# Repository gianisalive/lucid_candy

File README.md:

# Lucid Candy

A bare minimum 8 channel EEG board with TI ads1299 chip. It can be driven with any microcontroller that has 3.3V logic. Multiple boards can be chained together to record with 16 or 24 channels. This repository includes KiCad files and SPI example.

## Disclaimer
It still needs a lot of improvement, professional guidance and review. In no way it's fully tested to perform under clinical setting. Please use basic principles to test and evaluate before using it. All suggestions are highly appreciated: gianisalive@gmail.com

## Who should use it?
No one really should, but if you're a newbie in electronics, software, and neuroscience, and want to learn more by building, then this might be a thing for you. If you're just looking for an affordable EEG, there're better open source ones out there, such as [OpenBCI](https://openbci.com/).

## Files & Locations
|-- lucid_candy  
|---- component_datasheet------important datasheet of the components used for the board  
|---- e_component---------------all the KiCad pcb footprint (from SnapEDA) for the components  
|---- eeg------------------------KiCad design files  
|---- firmware-------------------example of Arduino DUE communicating with the board via SPI  
|---- gerber_zip-----------------same file used to produce the current board with JLCPCB  

## Schematics
The philosophy with current version of the design is to work within TI's recommendation, and choose components with least amount of tolerance/inductance to develope a baseline. In the future, any design improvement can be evaluated/compared to the current design.

## Components
All the component used can be found [here](https://docs.google.com/spreadsheets/d/1N4UGuHjUGolRgQoIL3MemhwEijfZmJlSR52b1LrSyF4/edit?usp=sharing). Some of these are pretty over priced. In most situations, you can probably get away with cheaper parts.

## Programming in a nutshell
**Overview:**  
- Data are transfered via SPI MODE1 with MSB first
- Data are retrieve with no-op command 0x00
- Chip has an internal clock. If BYOO (bring your own oscillator), then connect it to CLK pin, and tie CLKSEL low.  

**Power up sequence:**  
- Set CLKSEL pin high to enable internal oscillator
- Set RESET pin high, and make sure VCAP1 is settled around 1.1V
- Send reset command, and at this point DRDY pin should toggle at around 250Hz
- Send SDATAC (stop data continuous) command
- Set CONFIG1(0x01), CONFIG2(0x02) and CONFIG3(0x03)
- Set CHnSET (single ended, double ended or generate test signal)

**Data conversion:**  
- After sending RDATA or RDATAC command, data is returned on the second rising edge of the DRDY pin
- Initial 3 bytes are status data, and it always starts with 1100. Then it'll transfer 3 bytes of data per channel. An 8 channel board will have 8 * 3 + 3 = 27 bytes of data
- Data are structured in 2's compliment. The MSB is used to determin whether the value is positive or negative
- V = LSB * (2 * 4.5 / 24) / (2 ^ 24) // LSB = decimal value of 3 bytes channel data

## Testing
Fully assembled device with current Arduino firmware is tested with a calibrated Keysight DSOX1204G oscilloscope/function generator.

## Chanllenges
In a nutshell, eliminating noises and extracting the signal is one of the most chanllenging part when it comes to designing the hardware and the software.  
Neurons communcate via electrical signals (Action Potentials). When neurons are ready to send signals to neighboring neurons, they produce about 100 mV spike in less than 3 ms. These signals are further attenuated (reduction in signal strength) by the surrounding anatomical structures. When the electrode receives the signal, it's been attenuated to uV scale. In order to extract the signals, we need to filter out the noise with minimal distortion to the signal. There're few methods suggest that're yet to be implemented, such as bandpass filter, CleanLine and infinite impulse response.

## Miscellaneous
Some silly questions I asked:
 - [voltage offset](https://e2e.ti.com/support/data-converters/f/73/p/912858/3374371#3374371)

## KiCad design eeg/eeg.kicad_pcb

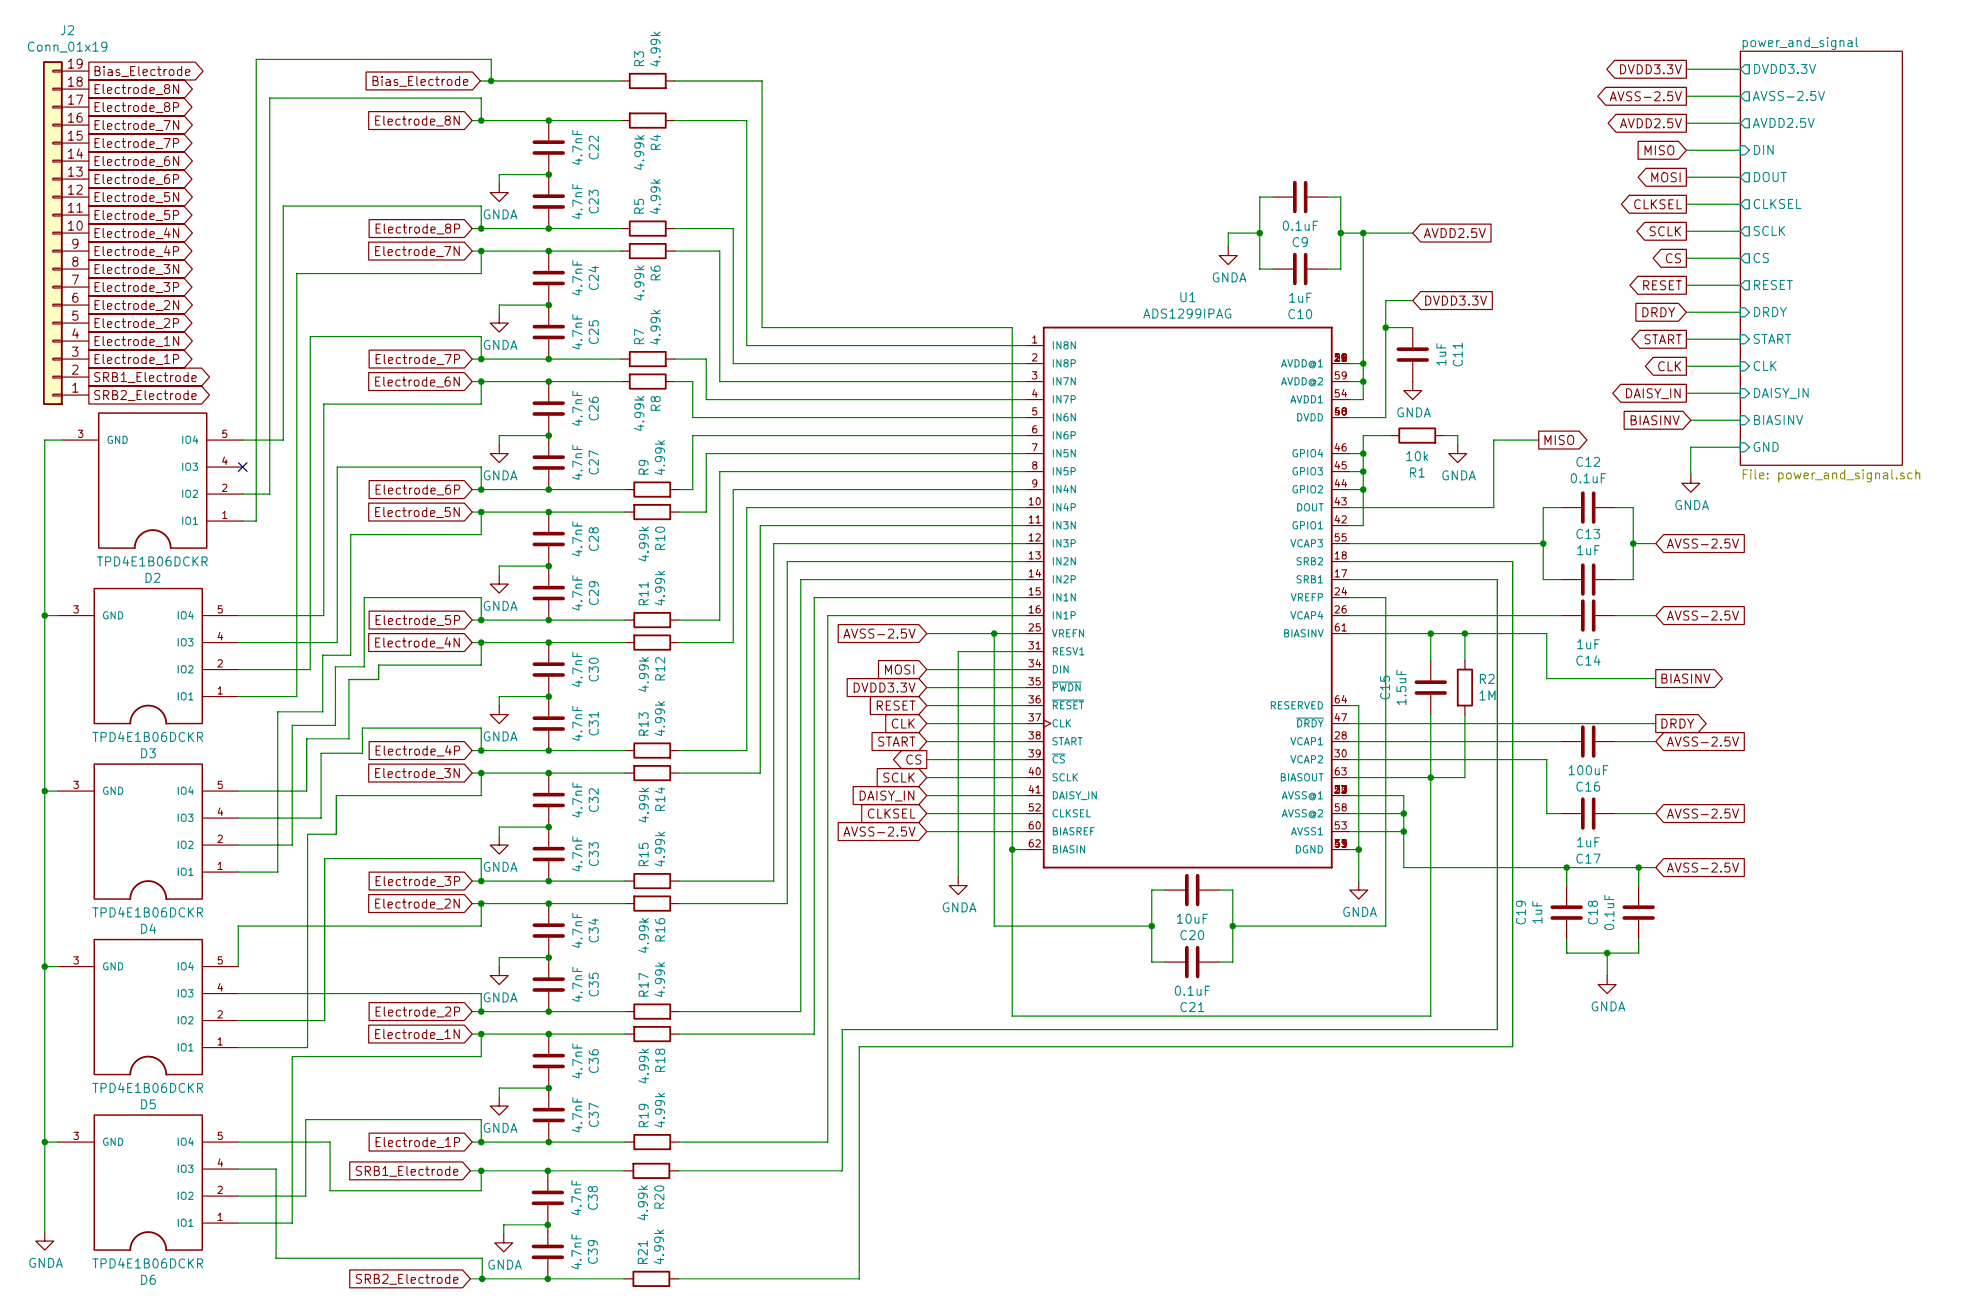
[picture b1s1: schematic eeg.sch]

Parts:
C9, C12, C18, C21: 0.1uF; C_0805_2012Metric_Pad1.15x1.40mm_HandSolder
C10, C11, C13, C14, C17, C19: 1uF; C_0805_2012Metric_Pad1.15x1.40mm_HandSolder
C15: 1.5uF; C_0805_2012Metric_Pad1.15x1.40mm_HandSolder
C16: 100uF; C_1210_3225Metric_Pad1.42x2.65mm_HandSolder
C20: 10uF; C_0805_2012Metric_Pad1.15x1.40mm_HandSolder
C22, C23, C24, C25, C26, C27, C28, C29, C30, C31, C32, C33, C34, C35, C36, C37, C38, C39: 4.7nF; C_0805_2012Metric_Pad1.15x1.40mm_HandSolder
D2, D3, D4, D5, D6: TPD4E1B06DCKR
J2: Conn_01x19; PinHeader_1x19_P2.54mm_Vertical
R1: 10k; R_0805_2012Metric_Pad1.15x1.40mm_HandSolder
R2: 1M; R_1206_3216Metric_Pad1.42x1.75mm_HandSolder
R3, R4, R5, R6, R7, R8, R9, R10, R11, R12, R13, R14, R15, R16, R17, R18, R19, R20, R21: 4.99k; R_0805_2012Metric_Pad1.15x1.40mm_HandSolder
U1: ADS1299IPAG

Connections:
AVDD2.5V: C9.1, C10.1, U1.19 (AVDD@1), U1.21 (AVDD@1), U1.22 (AVDD@1), U1.54 (AVDD1), U1.56 (AVDD@1), U1.59 (AVDD@2); also elsewhere on the board
AVSS-2.5V: C12.2, C13.2, C14.1, C16.1, C17.1, C18.2, C19.2, C20.2, C21.2, U1.20 (AVSS@1), U1.23 (AVSS@1), U1.25 (VREFN), U1.32 (AVSS@1), U1.53 (AVSS1), U1.57 (AVSS@1), U1.58 (AVSS@2), U1.60 (BIASREF); also elsewhere on the board
BIASINV: C15.2, R2.1, U1.61 (BIASINV); also elsewhere on the board
Bias_Electrode: D2.1 (IO1), J2.19, R3.1
CLK: U1.37 (CLK); also elsewhere on the board
CLKSEL: U1.52 (CLKSEL); also elsewhere on the board
CS: U1.39 (~CS~); also elsewhere on the board
DAISY_IN: U1.41 (DAISY_IN); also elsewhere on the board
DRDY: U1.47 (~DRDY~); also elsewhere on the board
DVDD3.3V: C11.1, U1.35 (~PWDN~), U1.48 (DVDD), U1.50 (DVDD); also elsewhere on the board
Electrode_1N: C36.1, D6.1 (IO1), J2.4, R18.2
Electrode_1P: C37.2, D6.2 (IO2), J2.3, R19.1
Electrode_2N: C34.1, D5.5 (IO4), J2.6, R16.2
Electrode_2P: C35.2, D5.4 (IO3), J2.5, R17.1
Electrode_3N: C32.1, D5.1 (IO1), J2.8, R14.2
Electrode_3P: C33.2, D5.2 (IO2), J2.7, R15.1
Electrode_4N: C30.1, D4.5 (IO4), J2.10, R12.2
Electrode_4P: C31.2, D4.4 (IO3), J2.9, R13.1
Electrode_5N: C28.1, D4.1 (IO1), J2.12, R10.2
Electrode_5P: C29.2, D4.2 (IO2), J2.11, R11.1
Electrode_6N: C26.1, D3.5 (IO4), J2.14, R8.2
Electrode_6P: C27.2, D3.4 (IO3), J2.13, R9.1
Electrode_7N: C24.1, D3.1 (IO1), J2.16, R6.2
Electrode_7P: C25.2, D3.2 (IO2), J2.15, R7.1
Electrode_8N: C22.1, D2.2 (IO2), J2.18, R4.2
Electrode_8P: C23.2, D2.5 (IO4), J2.17, R5.1
GNDA: C9.2, C10.2, C11.2, C18.1, C19.1, C22.2, C23.1, C24.2, C25.1, C26.2, C27.1, C28.2, C29.1, C30.2, C31.1, C32.2, C33.1, C34.2, C35.1, C36.2, C37.1, C38.2, C39.1, D2.3 (GND), D3.3 (GND), D4.3 (GND), D5.3 (GND), D6.3 (GND), R1.2, U1.31 (RESV1), U1.33 (DGND), U1.49 (DGND), U1.51 (DGND), U1.64 (RESERVED); also elsewhere on the board
MISO: U1.43 (DOUT); also elsewhere on the board
MOSI: U1.34 (DIN); also elsewhere on the board
unnamed: C12.1, C13.1, U1.55 (VCAP3)
unnamed: C14.2, U1.26 (VCAP4)
unnamed: C15.1, R2.2, R3.2, U1.62 (BIASIN), U1.63 (BIASOUT)
unnamed: C16.2, U1.28 (VCAP1)
unnamed: C17.2, U1.30 (VCAP2)
unnamed: C20.1, C21.1, U1.24 (VREFP)
unnamed: R1.1, U1.42 (GPIO1), U1.44 (GPIO2), U1.45 (GPIO3), U1.46 (GPIO4)
unnamed: R4.1, U1.1 (IN8N)
unnamed: R5.2, U1.2 (IN8P)
unnamed: R6.1, U1.3 (IN7N)
unnamed: R7.2, U1.4 (IN7P)
unnamed: R8.1, U1.5 (IN6N)
unnamed: R9.2, U1.6 (IN6P)
unnamed: R10.1, U1.7 (IN5N)
unnamed: R11.2, U1.8 (IN5P)
unnamed: R12.1, U1.9 (IN4N)
unnamed: R13.2, U1.10 (IN4P)
unnamed: R14.1, U1.11 (IN3N)
unnamed: R15.2, U1.12 (IN3P)
unnamed: R16.1, U1.13 (IN2N)
unnamed: R17.2, U1.14 (IN2P)
unnamed: R18.1, U1.15 (IN1N)
unnamed: R19.2, U1.16 (IN1P)
unnamed: R20.1, U1.17 (SRB1)
unnamed: R21.2, U1.18 (SRB2)
RESET: U1.36 (~RESET~); also elsewhere on the board
SCLK: U1.40 (SCLK); also elsewhere on the board
SRB1_Electrode: C38.1, D6.5 (IO4), J2.2, R20.2
SRB2_Electrode: C39.2, D6.4 (IO3), J2.1, R21.1
START: U1.38 (START); also elsewhere on the board

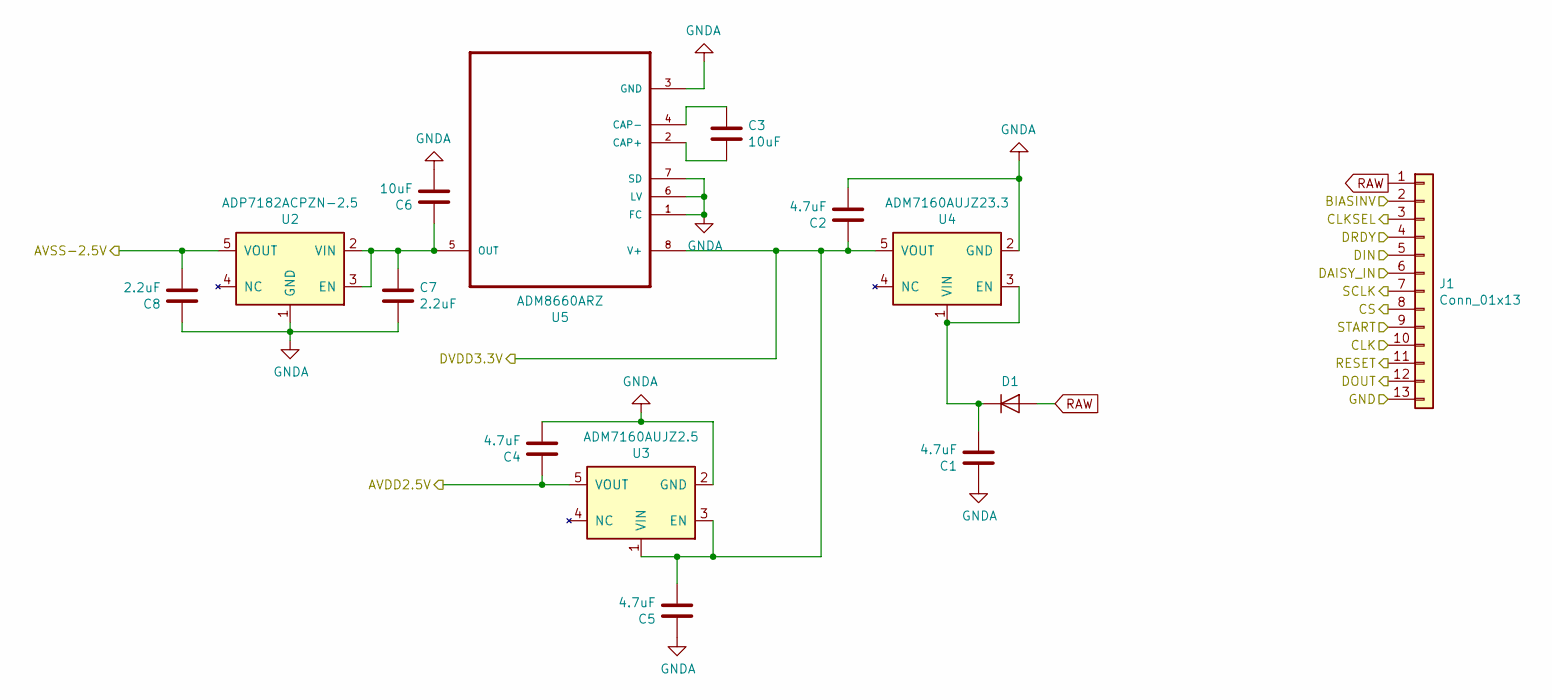
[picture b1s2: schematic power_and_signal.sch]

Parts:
C1, C2, C4, C5: 4.7uF; C_0805_2012Metric_Pad1.15x1.40mm_HandSolder
C3, C6: 10uF; C_0805_2012Metric_Pad1.15x1.40mm_HandSolder
C7, C8: 2.2uF; C_0805_2012Metric_Pad1.15x1.40mm_HandSolder
D1: D; D_SOD-523
J1: Conn_01x13; PinHeader_1x13_P2.54mm_Vertical
U2: ADP7182ACPZN-2.5; Analog_TSOT-5
U3: ADM7160AUJZ2.5; Analog_TSOT-5
U4: ADM7160AUJZ23.3; Analog_TSOT-5
U5: ADM8660ARZ

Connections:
AVDD2.5V: C4.1, U3.5 (VOUT); also elsewhere on the board
AVSS-2.5V: C8.2, U2.5 (VOUT); also elsewhere on the board
BIASINV: J1.2; also elsewhere on the board
CLK: J1.10; also elsewhere on the board
CLKSEL: J1.3; also elsewhere on the board
CS: J1.8; also elsewhere on the board
DAISY_IN: J1.6; also elsewhere on the board
DRDY: J1.4; also elsewhere on the board
DVDD3.3V: C2.1, C5.2, U3.1 (VIN), U3.3 (EN), U4.5 (VOUT), U5.8 (V+); also elsewhere on the board
GNDA: C1.1, C2.2, C4.2, C5.1, C6.2, C7.2, C8.1, J1.13, U2.1 (GND), U3.2 (GND), U4.2 (GND), U5.1 (FC), U5.3 (GND), U5.6 (LV), U5.7 (SD); also elsewhere on the board
MISO: J1.5; also elsewhere on the board
MOSI: J1.12; also elsewhere on the board
unnamed: C1.2, D1.1 (K), U4.1 (VIN), U4.3 (EN)
unnamed: C3.1, U5.4 (CAP-)
unnamed: C3.2, U5.2 (CAP+)
unnamed: C6.1, C7.1, U2.2 (VIN), U2.3 (EN), U5.5 (OUT)
RAW: D1.2 (A), J1.1
RESET: J1.11; also elsewhere on the board
SCLK: J1.7; also elsewhere on the board
START: J1.9; also elsewhere on the board

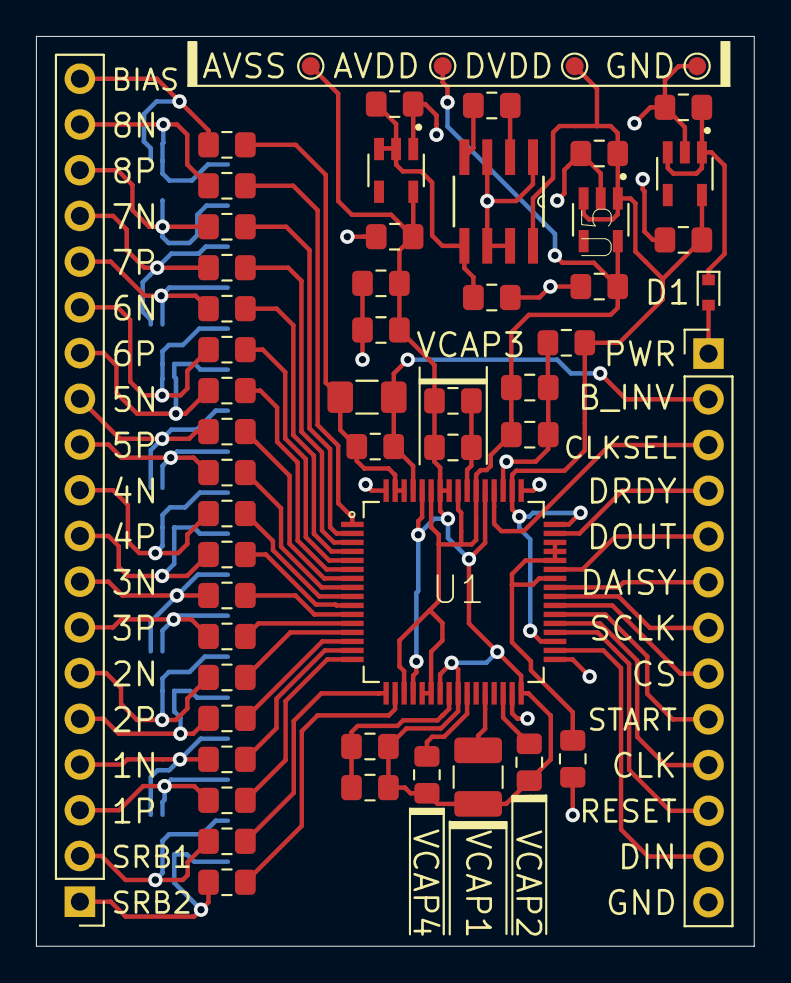
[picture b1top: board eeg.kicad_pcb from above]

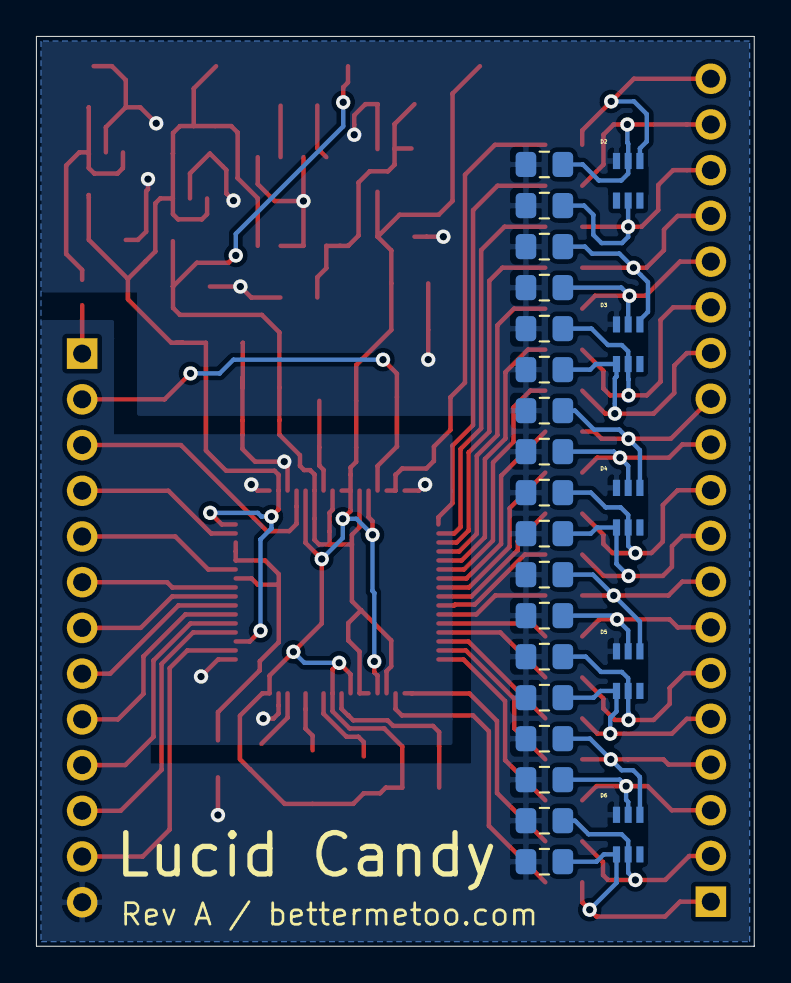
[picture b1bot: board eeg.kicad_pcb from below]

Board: 2 copper layers, 39.9 x 50.5 mm, 77 parts (23 on the bottom side), 64 nets.

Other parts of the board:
AVDD: TestPoint_Pad_D1.0mm
AVSS: TestPoint_Pad_D1.0mm
DVDD: TestPoint_Pad_D1.0mm
GND: TestPoint_Pad_D1.0mm

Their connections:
AVDD2.5V: AVDD.1; also elsewhere on the board
AVSS-2.5V: AVSS.1; also elsewhere on the board
DVDD3.3V: DVDD.1; also elsewhere on the board
GNDA: GND.1; also elsewhere on the board

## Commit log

2020-05-13 firmware sketch up
2020-05-14 get device ID, enable internal oscillator
2020-05-19 print device ID and read full byte of data
2020-05-20 add functions for read and write registers
2020-05-23 add read data continuous mode
2020-05-25 parse MISO data to 3 bytes hex
2020-06-07 convert digital to analog
2020-06-08 process two's compliment
2020-06-11 schematic
2020-06-11 differential config test
2020-06-17 add client serial read protocol
2020-06-18 adjust gain setting and improve power up sequence timing
2020-06-21 read data at 250hz
2020-06-21 test channel amplitude on start
2020-06-23 send device data via serial port upon request
2020-06-26 enable single ended mode and send eeg data upon request
2020-06-27 use compressed stream header
2020-06-29 send byte to client instead of ADC converted value
2020-07-15 read data in serial monitor
2020-07-20 separate code for serial monitor and serial transfer
2020-07-21 Fclean up
2020-07-21 include device schematic
2020-07-21 add jpg image
2020-07-21 product image
2020-07-29 allow channel number detection
2020-08-12 higher sample rate
2020-08-12 noise experiment
2020-08-14 scope setup and read data
